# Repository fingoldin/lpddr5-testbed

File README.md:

# LPDDR5 testbed for the ZCU104

A single-channel LPDDR5X module (currently targeting SK hynix H58G56BK7BX068N or Samsung K3KL8L80CM-MGCT, both 2 x 16 Gb
with one rank) on a card that plugs into the ZCU104's DDR4
SO-DIMM socket and is driven by the FPGA through a dedicated pin map. It is a custom LPDDR5 card, not a DDR4 memory
module.

### Goals

Implement custon PHY and controller on ZCU104 FPGA, communicate with one rank on one channel of the LPDDR5 package at
the highest command rate possible (up to 800 MHz, DDR). Reads and writes can be slow, but must be at least 20 Mb/s 
(WCK = 10 MHz). 

### High-level signal routing

FPGA <-> LPDDR5 routes, for one channel and one rank with no DM wires:
- Bank 64 on FPGA: command bus and write data -- CK, CA0-6, CS0, RESET_n, WCK0/1, DQ0-15, plus PWR_EN and PGOOD
  (33 of 37 pins, socket fingers 108-162). LPDDR5 balls are connected via a resistive divider to level-shift the FPGA
  signals down to ~0.5 V from 1.2 V.
- Bank 66 on FPGA: read data and strobes -- 16 DQ with RDQS0/1 as true pairs (18 of 20 pairs, socket fingers 169-250).
  LPDDR5 balls are connected directly to FPGA P pins, while the corresponding N pins carry VREF_RD from a static DAC
  defining the read reference value around 170 mV.
- Bank 65 on FPGA: spare (0 of 44 pins, socket fingers 3-84), free to take DMI or a second channel later.

### Board components

Resistive dividers for 

### Operating notes

LPDDR5 allows CK down to 5 MHz (tCK max 200 ns), but the data rate is tied to CK (4x or 8x), so reads and writes run in
their own frequency set point: CK 25 MHz for 100 Mb/s reads, 80 MHz for 320 Mb/s writes. 800 MHz CK is for
command-only traffic.

### File layout

| Folder | Contents |
|---|---|
| `references/` | data sheets, user guides, the JEDEC text, models and vendor PCB guidelines used for the design (`references/README.md`) |

Derived from the Antmicro LPDDR5 testbed.

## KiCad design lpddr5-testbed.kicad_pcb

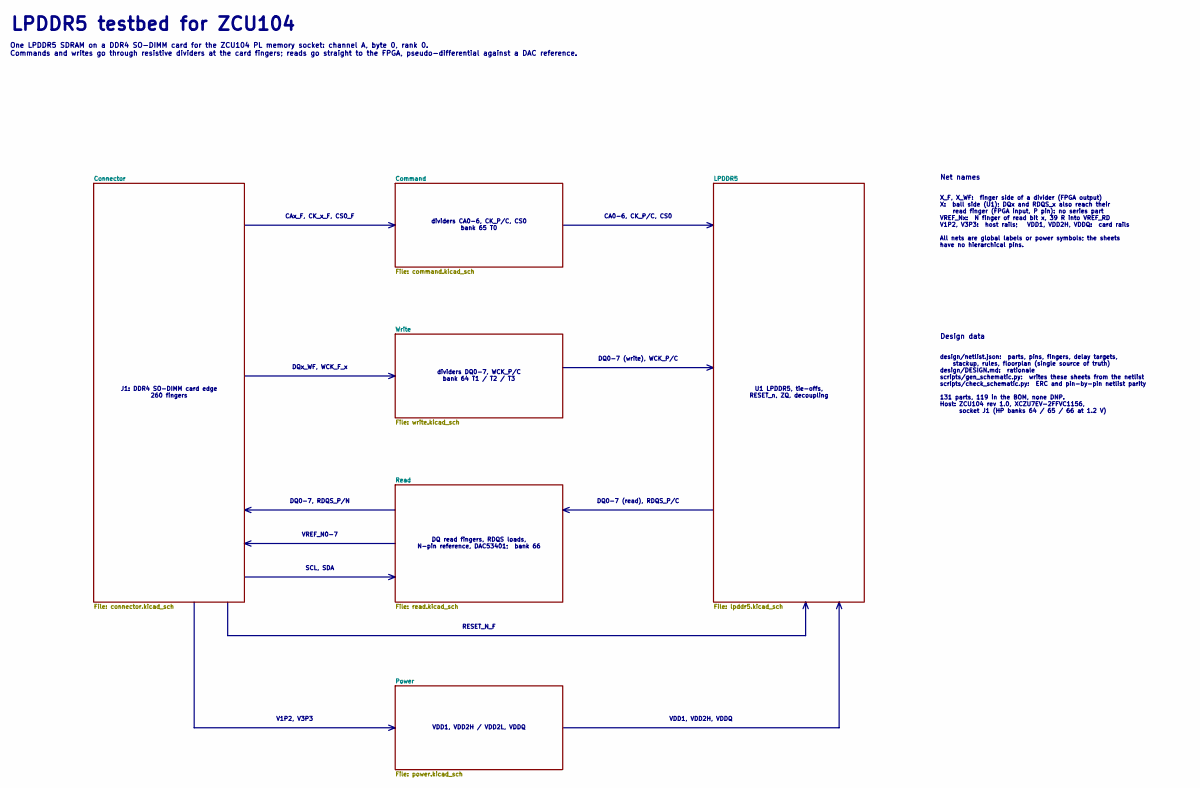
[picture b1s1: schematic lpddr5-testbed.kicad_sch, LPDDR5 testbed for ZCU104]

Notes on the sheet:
Net names
DQ0-7 (write), WCK_P/C
X_F, X_WF: finger side of a divider (FPGA output) X: ball side (U1); DQx and RDQS_x also reach their read finger (FPGA input, P pin): no series part VREF_Nx: N finger of read bit x, 39 R into VREF_RD V1P2, V3P3: host rails; VDD1, VDD2H, VDDQ: card rails All nets are global labels or power symbols; 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
DQ read fingers, RDQS loads, N-pin reference, DAC53401; bank 66
DQ0-7 (read), RDQS_P/C
CA0-6, CK_P/C, CS0
LPDDR5 testbed for ZCU104
CAx_F, CK_x_F, CS0_F
RESET_N_F
DQ0-7, RDQS_P/N
J1: DDR4 SO-DIMM card edge 260 fingers
V1P2, V3P3
VDD1, VDD2H / VDD2L, VDDQ
VREF_N0-7
Design data
SCL, SDA
design/netlist.json: parts, pins, fingers, delay targets, stackup, rules, floorplan (single source of truth) design/DESIGN.md: rationale scripts/gen_schematic.py: writes these sheets from the netlist scripts/check_schematic.py: ERC and pin-by-pin netlist parity 131 parts, 119 in the BOM, none DNP. 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
DQx_WF, WCK_F_x
dividers CA0-6, CK_P/C, CS0 bank 65 T0
dividers DQ0-7, WCK_P/C bank 64 T1 / T2 / T3
U1 LPDDR5, tie-offs, RESET_n, ZQ, decoupling
One LPDDR5 SDRAM on a DDR4 SO-DIMM card for the ZCU104 PL memory socket: channel A, byte 0, rank 0. Commands and writes go through resistive dividers at the card fingers; reads go straight to the FPGA, pseudo-differential against a DAC reference.
VDD1, VDD2H, VDDQ

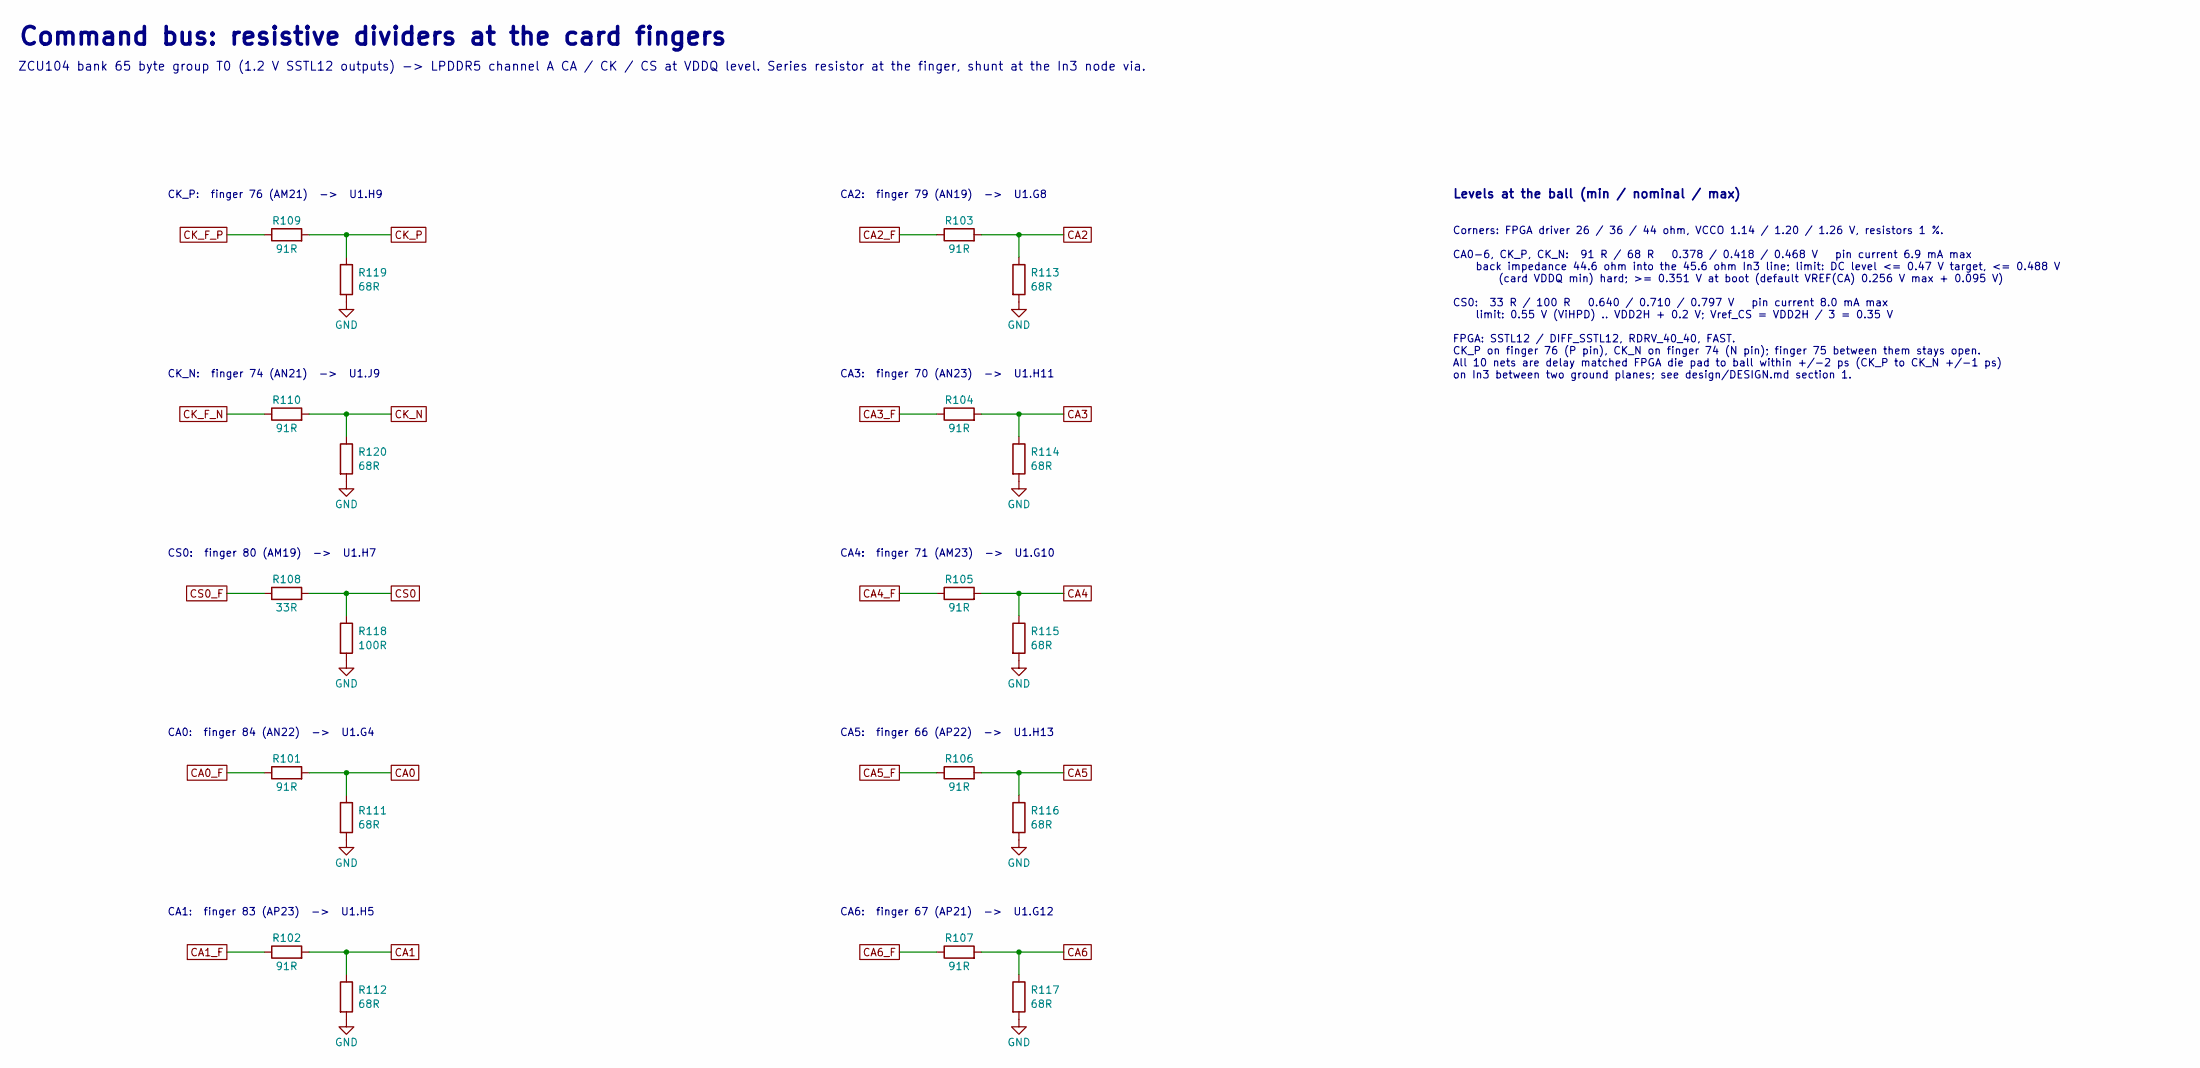
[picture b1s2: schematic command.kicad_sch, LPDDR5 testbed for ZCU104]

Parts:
R101, R102, R103, R104, R105, R106, R107, R109, R110: 91R; R_0201_0603Metric; MPN RC0201FR-0791RL
R108: 33R; R_0201_0603Metric; MPN RC0201FR-0733RL
R111, R112, R113, R114, R115, R116, R117, R119, R120: 68R; R_0201_0603Metric; MPN RC0201FR-0768RL
R118: 100R; R_0201_0603Metric; MPN RC0201FR-07100RL

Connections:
CA0: R101.2, R111.1; also elsewhere on the board
CA0_F: R101.1; also elsewhere on the board
CA1: R102.2, R112.1; also elsewhere on the board
CA1_F: R102.1; also elsewhere on the board
CA2: R103.2, R113.1; also elsewhere on the board
CA2_F: R103.1; also elsewhere on the board
CA3: R104.2, R114.1; also elsewhere on the board
CA3_F: R104.1; also elsewhere on the board
CA4: R105.2, R115.1; also elsewhere on the board
CA4_F: R105.1; also elsewhere on the board
CA5: R106.2, R116.1; also elsewhere on the board
CA5_F: R106.1; also elsewhere on the board
CA6: R107.2, R117.1; also elsewhere on the board
CA6_F: R107.1; also elsewhere on the board
CK_F_N: R110.1; also elsewhere on the board
CK_F_P: R109.1; also elsewhere on the board
CK_N: R110.2, R120.1; also elsewhere on the board
CK_P: R109.2, R119.1; also elsewhere on the board
CS0: R108.2, R118.1; also elsewhere on the board
CS0_F: R108.1; also elsewhere on the board
GND: R111.2, R112.2, R113.2, R114.2, R115.2, R116.2, R117.2, R118.2, R119.2, R120.2; also elsewhere on the board

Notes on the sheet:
CS0: finger 80 (AM19) -> U1.H7
CA0: finger 84 (AN22) -> U1.G4
Corners: FPGA driver 26 / 36 / 44 ohm, VCCO 1.14 / 1.20 / 1.26 V, resistors 1 %. CA0-6, CK_P, CK_N: 91 R / 68 R 0.378 / 0.418 / 0.468 V pin current 6.9 mA max back impedance 44.6 ohm into the 45.6 ohm In3 line; limit: DC level <= 0.47 V target, <= 0.488 V (card VDDQ min) hard; >= 0.351 V at boot (d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
CA6: finger 67 (AP21) -> U1.G12
Command bus: resistive dividers at the card fingers
CA4: finger 71 (AM23) -> U1.G10
CK_N: finger 74 (AN21) -> U1.J9
ZCU104 bank 65 byte group T0 (1.2 V SSTL12 outputs) -> LPDDR5 channel A CA / CK / CS at VDDQ level. Series resistor at the finger, shunt at the In3 node via.
CA1: finger 83 (AP23) -> U1.H5
Levels at the ball (min / nominal / max)
CK_P: finger 76 (AM21) -> U1.H9
CA2: finger 79 (AN19) -> U1.G8
CA5: finger 66 (AP22) -> U1.H13
CA3: finger 70 (AN23) -> U1.H11

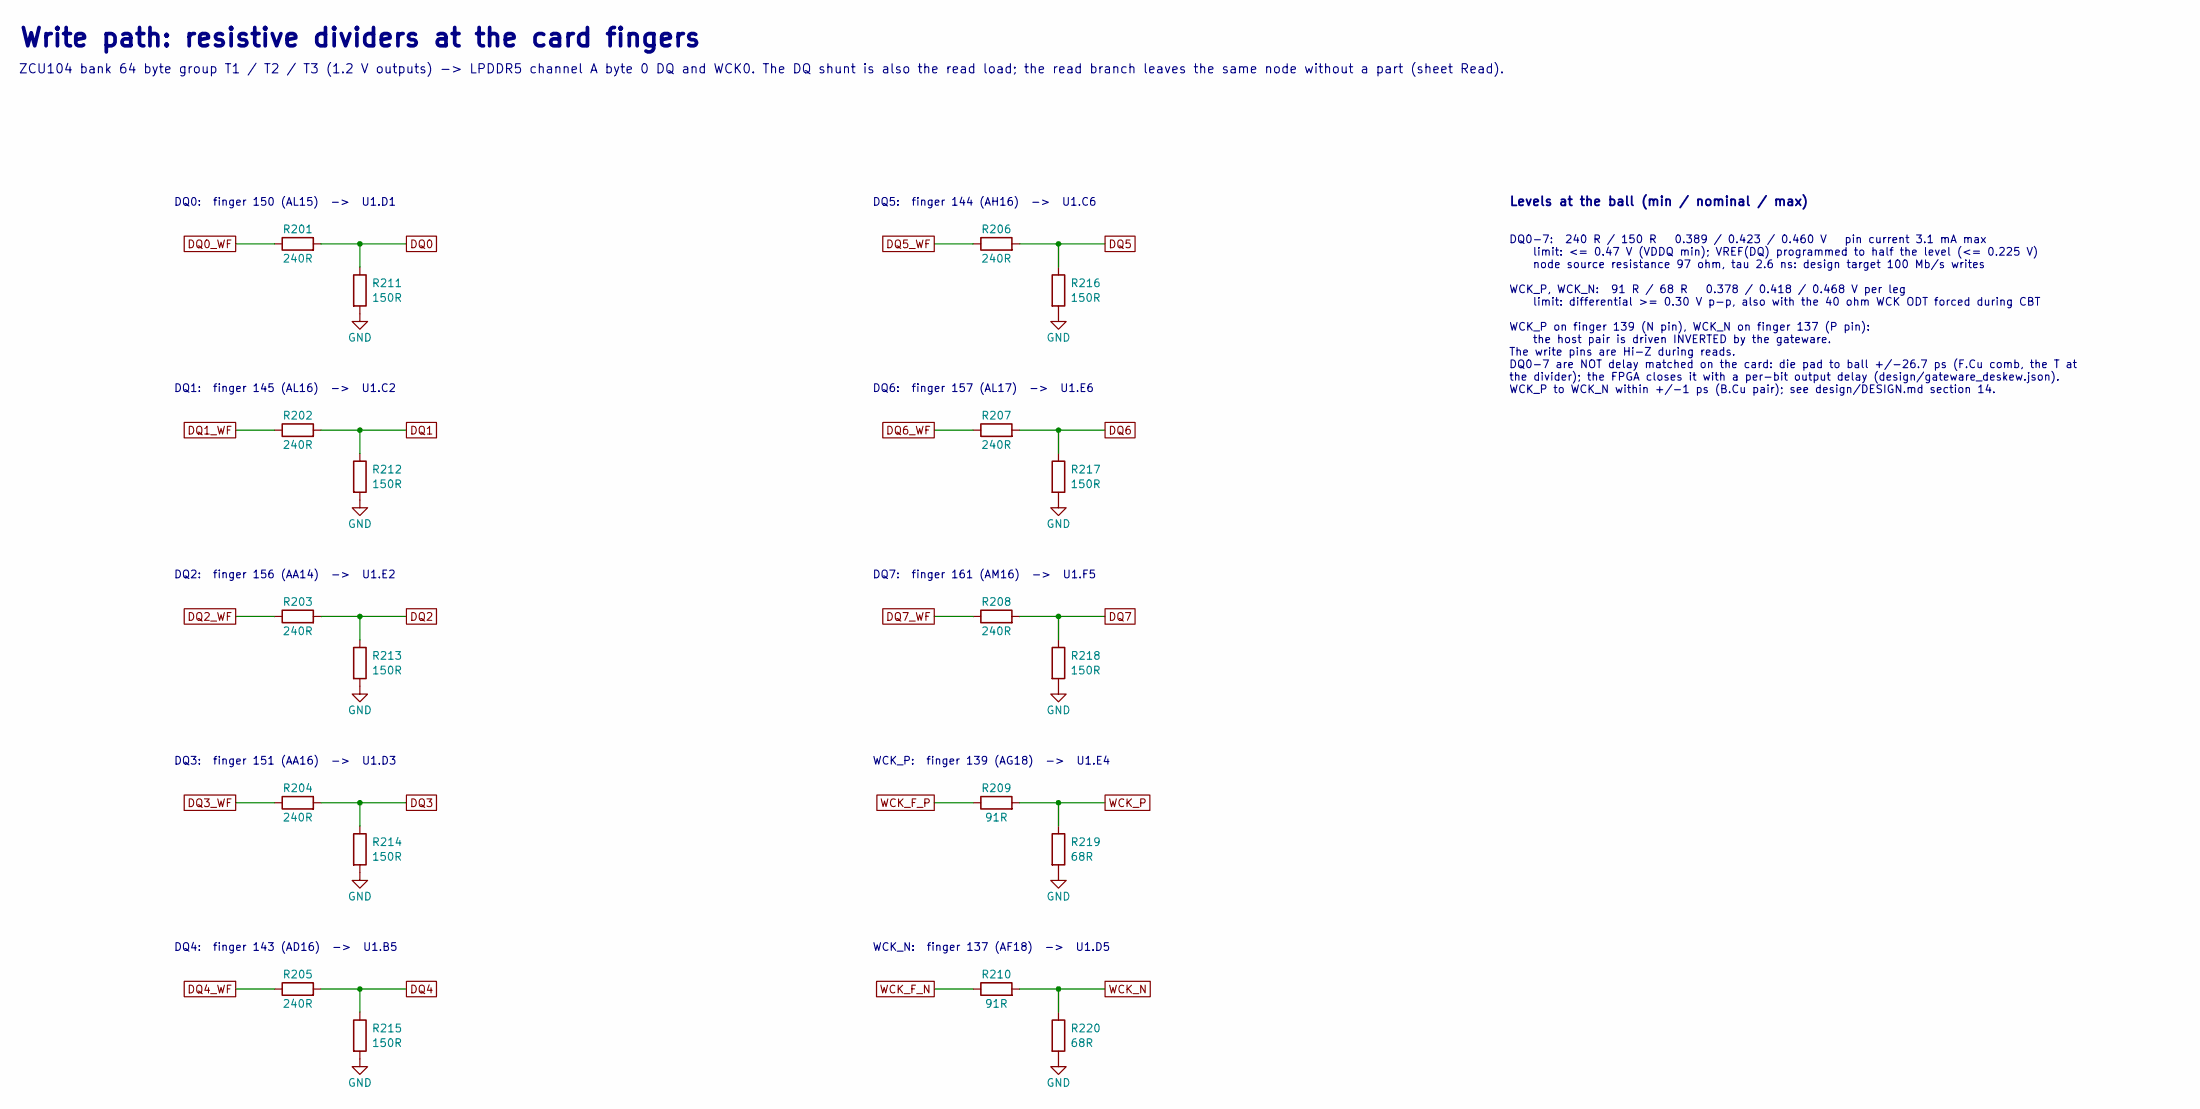
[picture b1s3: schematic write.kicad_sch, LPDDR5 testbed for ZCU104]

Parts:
R201, R202, R203, R204, R205, R206, R207, R208: 240R; R_0201_0603Metric; MPN RC0201FR-07240RL
R209, R210: 91R; R_0201_0603Metric; MPN RC0201FR-0791RL
R211, R212, R213, R214, R215, R216, R217, R218: 150R; R_0201_0603Metric; MPN RC0201FR-07150RL
R219, R220: 68R; R_0201_0603Metric; MPN RC0201FR-0768RL

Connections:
DQ0: R201.2, R211.1; also elsewhere on the board
DQ0_WF: R201.1; also elsewhere on the board
DQ1: R202.2, R212.1; also elsewhere on the board
DQ1_WF: R202.1; also elsewhere on the board
DQ2: R203.2, R213.1; also elsewhere on the board
DQ2_WF: R203.1; also elsewhere on the board
DQ3: R204.2, R214.1; also elsewhere on the board
DQ3_WF: R204.1; also elsewhere on the board
DQ4: R205.2, R215.1; also elsewhere on the board
DQ4_WF: R205.1; also elsewhere on the board
DQ5: R206.2, R216.1; also elsewhere on the board
DQ5_WF: R206.1; also elsewhere on the board
DQ6: R207.2, R217.1; also elsewhere on the board
DQ6_WF: R207.1; also elsewhere on the board
DQ7: R208.2, R218.1; also elsewhere on the board
DQ7_WF: R208.1; also elsewhere on the board
GND: R211.2, R212.2, R213.2, R214.2, R215.2, R216.2, R217.2, R218.2, R219.2, R220.2; also elsewhere on the board
WCK_F_N: R210.1; also elsewhere on the board
WCK_F_P: R209.1; also elsewhere on the board
WCK_N: R210.2, R220.1; also elsewhere on the board
WCK_P: R209.2, R219.1; also elsewhere on the board

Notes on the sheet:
DQ4: finger 143 (AD16) -> U1.B5
ZCU104 bank 64 byte group T1 / T2 / T3 (1.2 V outputs) -> LPDDR5 channel A byte 0 DQ and WCK0. The DQ shunt is also the read load; the read branch leaves the same node without a part (sheet Read).
DQ5: finger 144 (AH16) -> U1.C6
Write path: resistive dividers at the card fingers
DQ6: finger 157 (AL17) -> U1.E6
DQ0: finger 150 (AL15) -> U1.D1
WCK_N: finger 137 (AF18) -> U1.D5
DQ7: finger 161 (AM16) -> U1.F5
DQ1: finger 145 (AL16) -> U1.C2
DQ2: finger 156 (AA14) -> U1.E2
Levels at the ball (min / nominal / max)
DQ3: finger 151 (AA16) -> U1.D3
DQ0-7: 240 R / 150 R 0.389 / 0.423 / 0.460 V pin current 3.1 mA max limit: <= 0.47 V (VDDQ min); VREF(DQ) programmed to half the level (<= 0.225 V) node source resistance 97 ohm, tau 2.6 ns: design target 100 Mb/s writes WCK_P, WCK_N: 91 R / 68 R 0.378 / 0.418 / 0.468 V per leg limit: differential 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
WCK_P: finger 139 (AG18) -> U1.E4

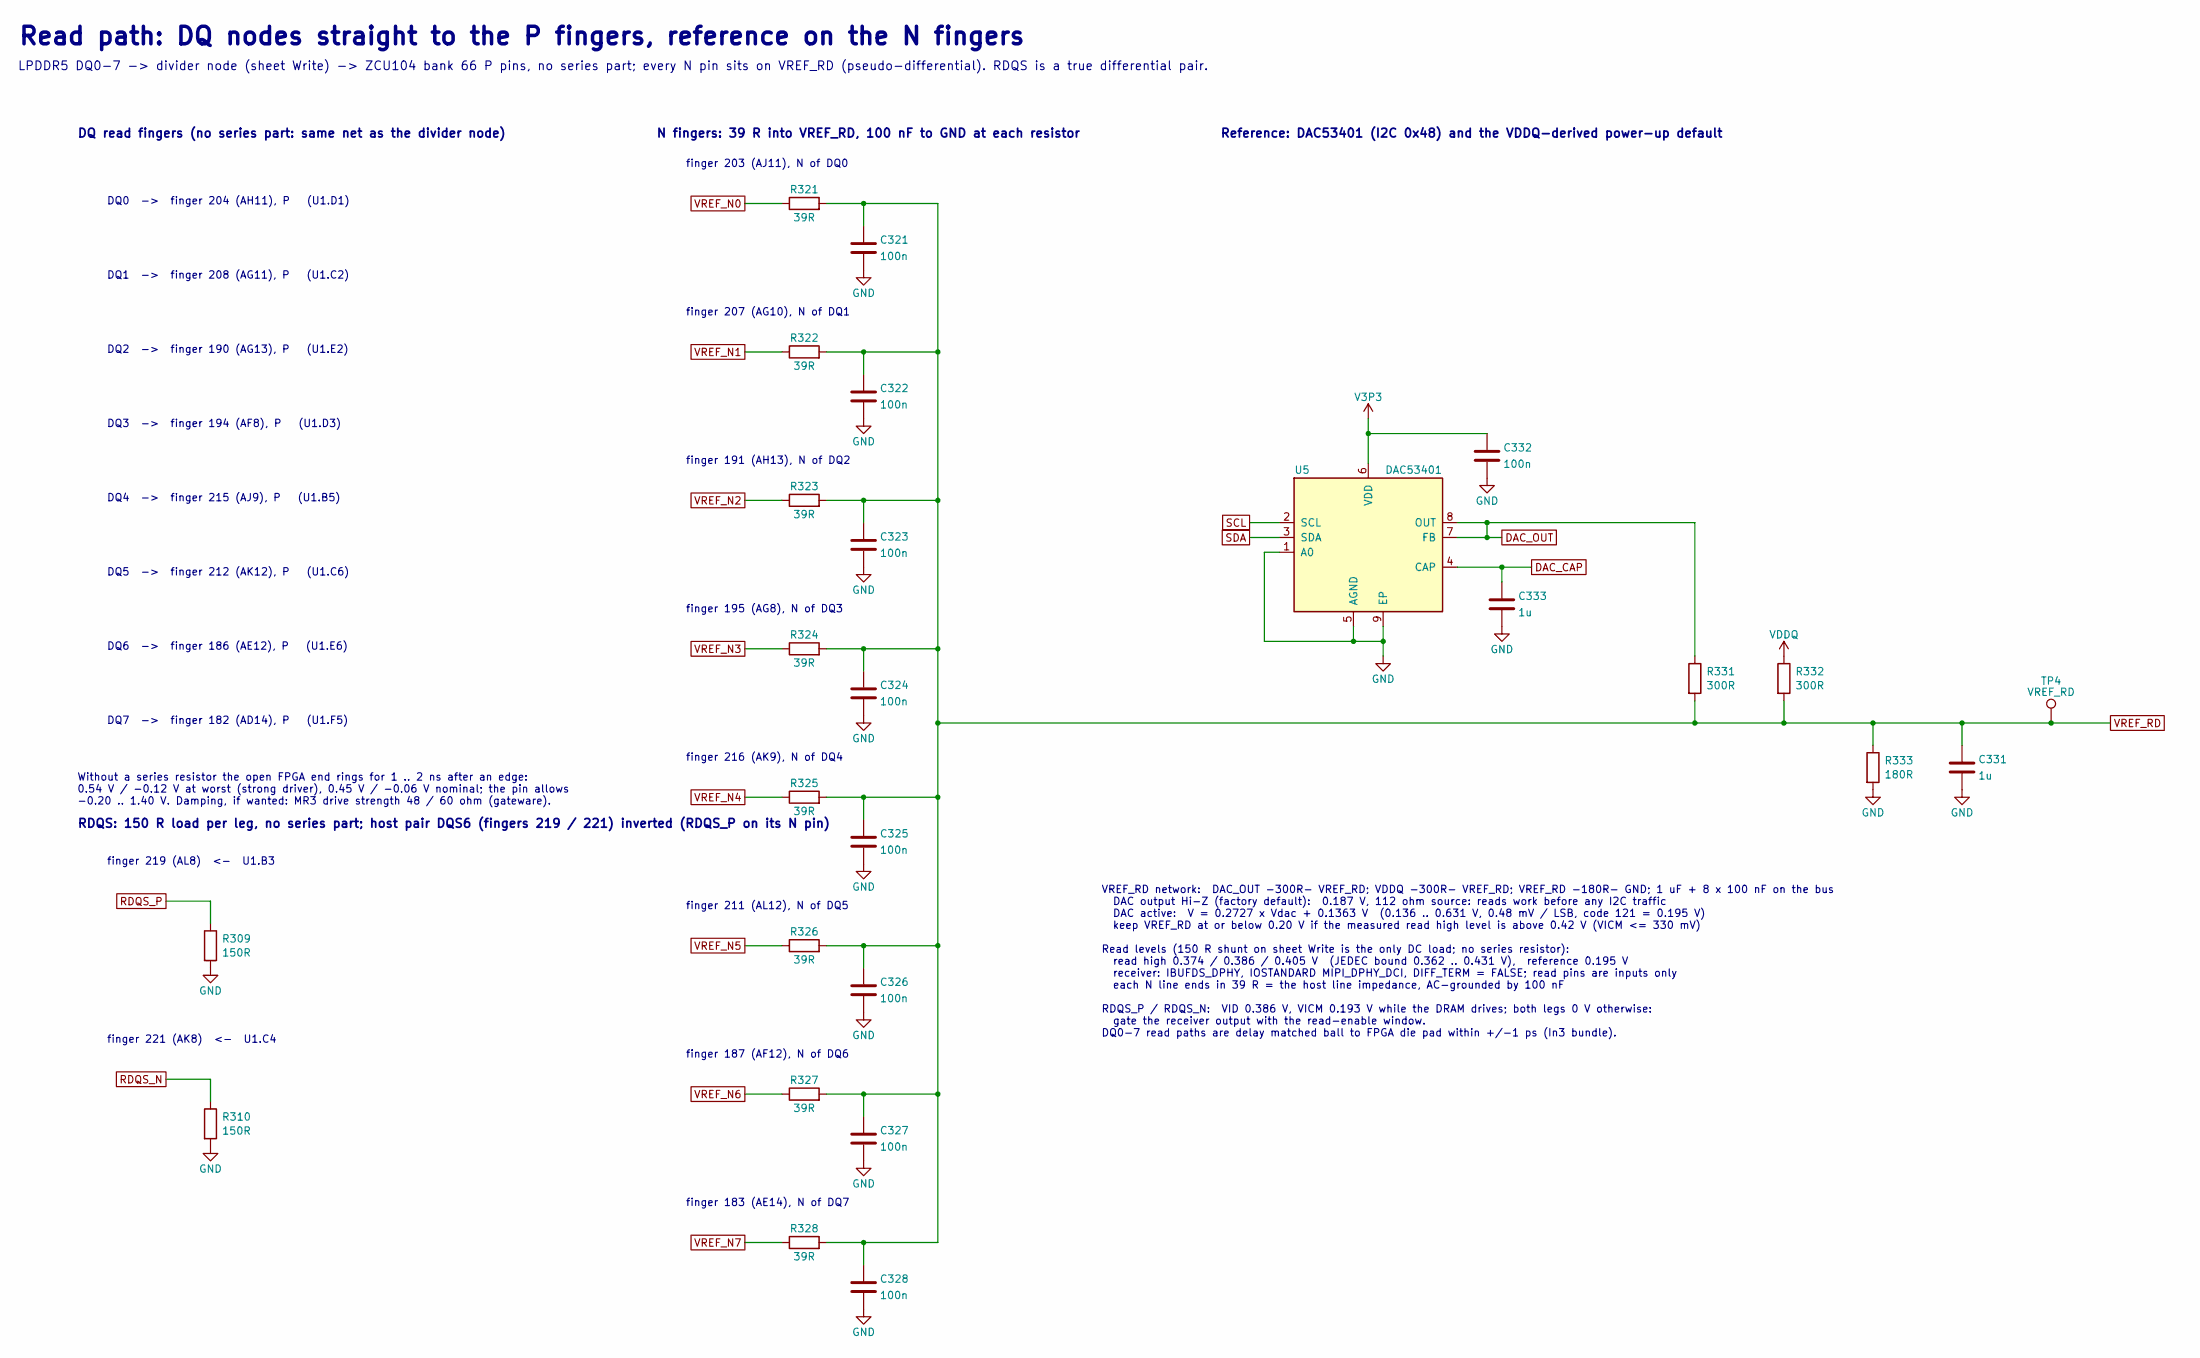
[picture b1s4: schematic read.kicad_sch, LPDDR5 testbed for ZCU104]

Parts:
C321, C322, C323, C324, C325, C326, C327, C328: 100n; C_0201_0603Metric; MPN CL03A104KQ3NNNC
C331, C333: 1u; C_0402_1005Metric; MPN CL05A105KP5NNNC
C332: 100n; C_0402_1005Metric; MPN CL05B104KO5NNNC
R309, R310: 150R; R_0201_0603Metric; MPN RC0201FR-07150RL
R321, R322, R323, R324, R325, R326, R327, R328: 39R; R_0201_0603Metric; MPN RC0201FR-0739RL
R331, R332: 300R; R_0402_1005Metric; MPN RC0402FR-07300RL
R333: 180R; R_0402_1005Metric; MPN RC0402FR-07180RL
TP4: VREF_RD; TestPoint_Pad_D1.0mm; MPN N/A (PCB pad)
U5: DAC53401; WSON-8-1EP_2x2mm_P0.5mm_EP0.9x1.6mm; MPN DAC53401DSGR

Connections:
DAC_CAP: C333.1, U5.4 (CAP)
DAC_OUT: R331.1, U5.7 (FB), U5.8 (OUT)
GND: C321.2, C322.2, C323.2, C324.2, C325.2, C326.2, C327.2, C328.2, C331.2, C332.2, C333.2, R309.2, R310.2, R333.2, U5.1 (A0), U5.5 (AGND), U5.9 (EP); also elsewhere on the board
RDQS_N: R310.1; also elsewhere on the board
RDQS_P: R309.1; also elsewhere on the board
SCL: U5.2 (SCL); also elsewhere on the board
SDA: U5.3 (SDA); also elsewhere on the board
V3P3: C332.1, U5.6 (VDD); also elsewhere on the board
VDDQ: R332.1; also elsewhere on the board
VREF_N0: R321.1; also elsewhere on the board
VREF_N1: R322.1; also elsewhere on the board
VREF_N2: R323.1; also elsewhere on the board
VREF_N3: R324.1; also elsewhere on the board
VREF_N4: R325.1; also elsewhere on the board
VREF_N5: R326.1; also elsewhere on the board
VREF_N6: R327.1; also elsewhere on the board
VREF_N7: R328.1; also elsewhere on the board
VREF_RD: C321.1, C322.1, C323.1, C324.1, C325.1, C326.1, C327.1, C328.1, C331.1, R321.2, R322.2, R323.2, R324.2, R325.2, R326.2, R327.2, R328.2, R331.2, R332.2, R333.1, TP4.1

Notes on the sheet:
DQ7 -> finger 182 (AD14), P (U1.F5)
DQ1 -> finger 208 (AG11), P (U1.C2)
Reference: DAC53401 (I2C 0x48) and the VDDQ-derived power-up default
RDQS: 150 R load per leg, no series part; host pair DQS6 (fingers 219 / 221) inverted (RDQS_P on its N pin)
Without a series resistor the open FPGA end rings for 1 .. 2 ns after an edge: 0.54 V / -0.12 V at worst (strong driver), 0.45 V / -0.06 V nominal; the pin allows -0.20 .. 1.40 V. Damping, if wanted: MR3 drive strength 48 / 60 ohm (gateware).
N fingers: 39 R into VREF_RD, 100 nF to GND at each resistor
LPDDR5 DQ0-7 -> divider node (sheet Write) -> ZCU104 bank 66 P pins, no series part; every N pin sits on VREF_RD (pseudo-differential). RDQS is a true differential pair.
VREF_RD network: DAC_OUT -300R- VREF_RD; VDDQ -300R- VREF_RD; VREF_RD -180R- GND; 1 uF + 8 x 100 nF on the bus DAC output Hi-Z (factory default): 0.187 V, 112 ohm source: reads work before any I2C traffic DAC active: V = 0.2727 x Vdac + 0.1363 V (0.136 .. 0.631 V, 0.48 mV / LSB, code 121 = 0.195 V)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
finger 195 (AG8), N of DQ3
DQ2 -> finger 190 (AG13), P (U1.E2)
finger 211 (AL12), N of DQ5
finger 203 (AJ11), N of DQ0
finger 191 (AH13), N of DQ2
finger 221 (AK8) <- U1.C4
DQ0 -> finger 204 (AH11), P (U1.D1)
DQ5 -> finger 212 (AK12), P (U1.C6)
DQ6 -> finger 186 (AE12), P (U1.E6)
DQ4 -> finger 215 (AJ9), P (U1.B5)
finger 183 (AE14), N of DQ7
DQ read fingers (no series part: same net as the divider node)
finger 207 (AG10), N of DQ1
Read path: DQ nodes straight to the P fingers, reference on the N fingers
finger 216 (AK9), N of DQ4
finger 219 (AL8) <- U1.B3
DQ3 -> finger 194 (AF8), P (U1.D3)
finger 187 (AF12), N of DQ6

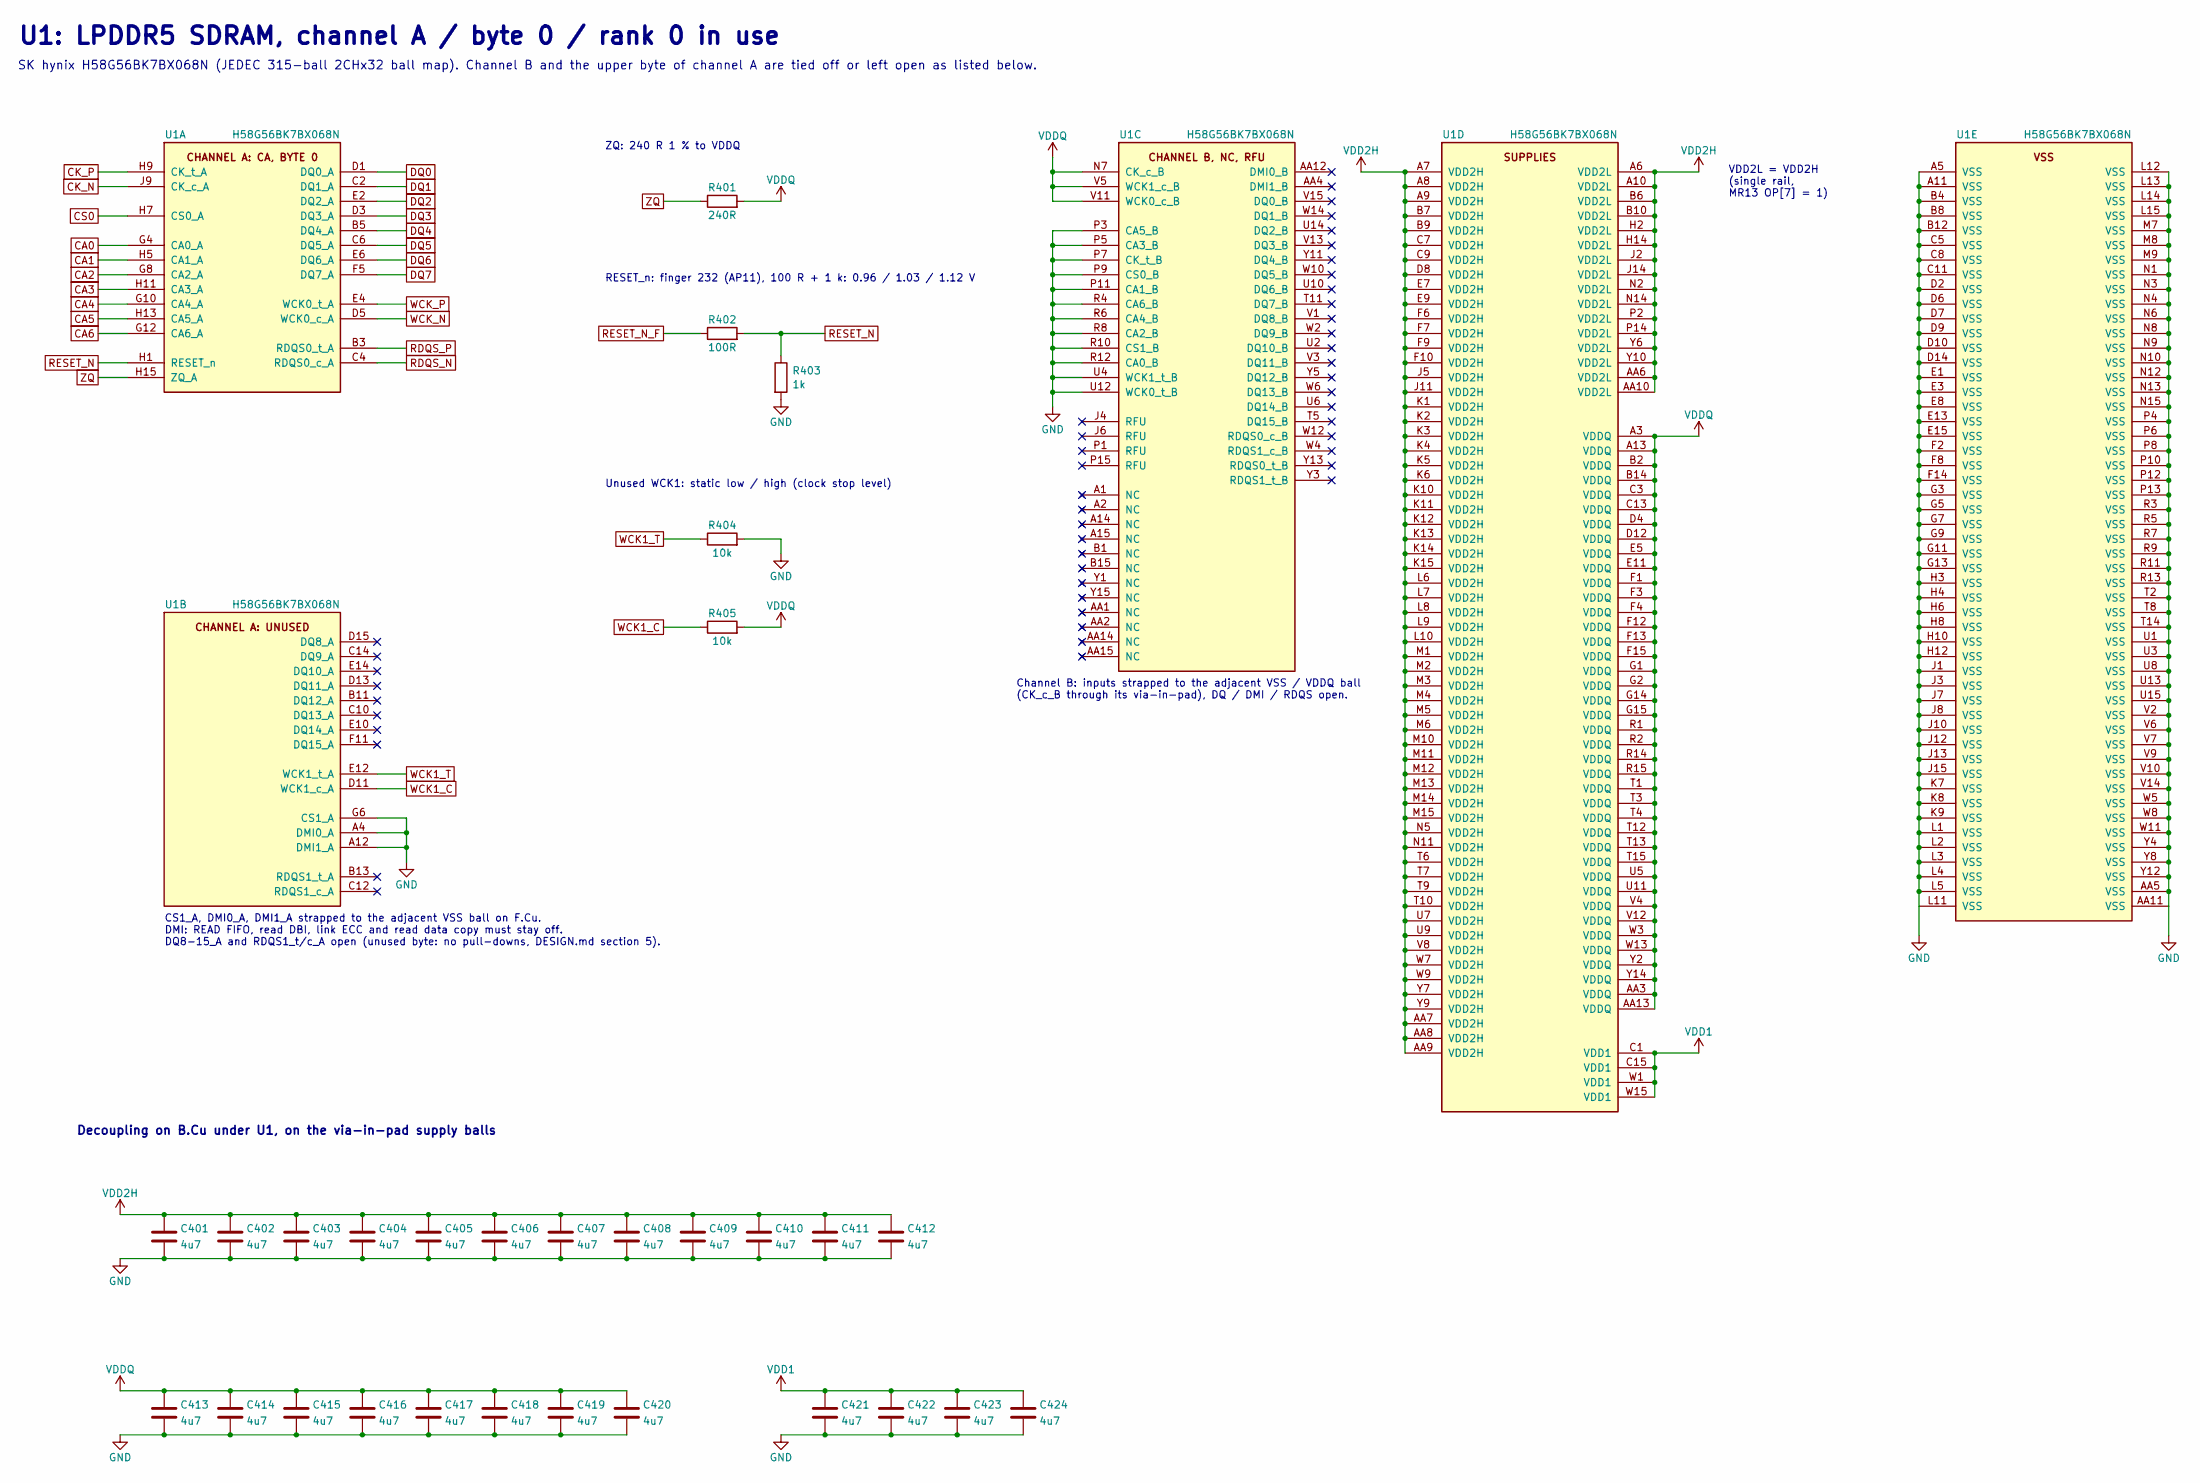
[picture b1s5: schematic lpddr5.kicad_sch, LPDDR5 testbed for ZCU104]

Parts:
C401, C402, C403, C404, C405, C406, C407, C408, C409, C410, C411, C412, C413, C414, C415, C416, C417, C418, C419, C420, C421, C422, C423, C424: 4u7; C_0402_1005Metric; MPN CL05A475MP5NRNC
R401: 240R; R_0201_0603Metric; MPN RC0201FR-07240RL
R402: 100R; R_0201_0603Metric; MPN RC0201FR-07100RL
R403: 1k; R_0402_1005Metric; MPN RC0402FR-071KL
R404, R405: 10k; R_0402_1005Metric; MPN RC0402FR-0710KL
U1: H58G56BK7BX068N; BGA-315_12.4x15mm_P0.8x0.7mm; MPN H58G56BK7BX068N

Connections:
CA0: U1.G4 (CA0_A); also elsewhere on the board
CA1: U1.H5 (CA1_A); also elsewhere on the board
CA2: U1.G8 (CA2_A); also elsewhere on the board
CA3: U1.H11 (CA3_A); also elsewhere on the board
CA4: U1.G10 (CA4_A); also elsewhere on the board
CA5: U1.H13 (CA5_A); also elsewhere on the board
CA6: U1.G12 (CA6_A); also elsewhere on the board
CK_N: U1.J9 (CK_c_A); also elsewhere on the board
CK_P: U1.H9 (CK_t_A); also elsewhere on the board
CS0: U1.H7 (CS0_A); also elsewhere on the board
DQ0: U1.D1 (DQ0_A); also elsewhere on the board
DQ1: U1.C2 (DQ1_A); also elsewhere on the board
DQ2: U1.E2 (DQ2_A); also elsewhere on the board
DQ3: U1.D3 (DQ3_A); also elsewhere on the board
DQ4: U1.B5 (DQ4_A); also elsewhere on the board
DQ5: U1.C6 (DQ5_A); also elsewhere on the board
DQ6: U1.E6 (DQ6_A); also elsewhere on the board
DQ7: U1.F5 (DQ7_A); also elsewhere on the board
GND: C401.2, C402.2, C403.2, C404.2, C405.2, C406.2, C407.2, C408.2, C409.2, C410.2, C411.2, C412.2, C413.2, C414.2, C415.2, C416.2, C417.2, C418.2, C419.2, C420.2, C421.2, C422.2, C423.2, C424.2, R403.2, R404.2, U1.A4 (DMI0_A), U1.A5 (VSS), U1.A11 (VSS), U1.A12 (DMI1_A), U1.AA5 (VSS), U1.AA11 (VSS), U1.B4 (VSS), U1.B8 (VSS), U1.B12 (VSS), U1.C5 (VSS), U1.C8 (VSS), U1.C11 (VSS), U1.D2 (VSS), U1.D6 (VSS), U1.D7 (VSS), U1.D9 (VSS), U1.D10 (VSS), U1.D14 (VSS), U1.E1 (VSS), U1.E3 (VSS), U1.E8 (VSS), U1.E13 (VSS), U1.E15 (VSS), U1.F2 (VSS), U1.F8 (VSS), U1.F14 (VSS), U1.G3 (VSS), U1.G5 (VSS), U1.G6 (CS1_A), U1.G7 (VSS), U1.G9 (VSS), U1.G11 (VSS), U1.G13 (VSS), U1.H3 (VSS), U1.H4 (VSS), U1.H6 (VSS), U1.H8 (VSS), U1.H10 (VSS), U1.H12 (VSS), U1.J1 (VSS), U1.J3 (VSS), U1.J7 (VSS), U1.J8 (VSS), U1.J10 (VSS), U1.J12 (VSS), U1.J13 (VSS), U1.J15 (VSS), U1.K7 (VSS), U1.K8 (VSS), U1.K9 (VSS), U1.L1 (VSS), U1.L2 (VSS), U1.L3 (VSS), U1.L4 (VSS), U1.L5 (VSS), U1.L11 (VSS), U1.L12 (VSS), U1.L13 (VSS), U1.L14 (VSS), U1.L15 (VSS), U1.M7 (VSS), U1.M8 (VSS), U1.M9 (VSS), U1.N1 (VSS), U1.N3 (VSS), U1.N4 (VSS), U1.N6 (VSS), U1.N8 (VSS), U1.N9 (VSS), U1.N10 (VSS), U1.N12 (VSS), U1.N13 (VSS), U1.N15 (VSS), U1.P3 (CA5_B), U1.P4 (VSS), U1.P5 (CA3_B), U1.P6 (VSS), U1.P7 (CK_t_B), U1.P8 (VSS), U1.P9 (CS0_B), U1.P10 (VSS), U1.P11 (CA1_B), U1.P12 (VSS), U1.P13 (VSS), U1.R3 (VSS), U1.R4 (CA6_B), U1.R5 (VSS), U1.R6 (CA4_B), U1.R7 (VSS), U1.R8 (CA2_B), U1.R9 (VSS), U1.R10 (CS1_B), U1.R11 (VSS), U1.R12 (CA0_B), U1.R13 (VSS), U1.T2 (VSS), U1.T8 (VSS), U1.T14 (VSS), U1.U1 (VSS), U1.U3 (VSS), U1.U4 (WCK1_t_B), U1.U8 (VSS), U1.U12 (WCK0_t_B), U1.U13 (VSS), U1.U15 (VSS), U1.V2 (VSS), U1.V6 (VSS), U1.V7 (VSS), U1.V9 (VSS), U1.V10 (VSS), U1.V14 (VSS), U1.W5 (VSS), U1.W8 (VSS), U1.W11 (VSS), U1.Y4 (VSS), U1.Y8 (VSS), U1.Y12 (VSS); also elsewhere on the board
RDQS_N: U1.C4 (RDQS0_c_A); also elsewhere on the board
RDQS_P: U1.B3 (RDQS0_t_A); also elsewhere on the board
RESET_N: R402.2, R403.1, U1.H1 (RESET_n)
RESET_N_F: R402.1; also elsewhere on the board
VDD1: C421.1, C422.1, C423.1, C424.1, U1.C1 (VDD1), U1.C15 (VDD1), U1.W1 (VDD1), U1.W15 (VDD1); also elsewhere on the board
VDD2H: C401.1, C402.1, C403.1, C404.1, C405.1, C406.1, C407.1, C408.1, C409.1, C410.1, C411.1, C412.1, U1.A6 (VDD2L), U1.A7 (VDD2H), U1.A8 (VDD2H), U1.A9 (VDD2H), U1.A10 (VDD2L), U1.AA6 (VDD2L), U1.AA7 (VDD2H), U1.AA8 (VDD2H), U1.AA9 (VDD2H), U1.AA10 (VDD2L), U1.B6 (VDD2L), U1.B7 (VDD2H), U1.B9 (VDD2H), U1.B10 (VDD2L), U1.C7 (VDD2H), U1.C9 (VDD2H), U1.D8 (VDD2H), U1.E7 (VDD2H), U1.E9 (VDD2H), U1.F6 (VDD2H), U1.F7 (VDD2H), U1.F9 (VDD2H), U1.F10 (VDD2H), U1.H2 (VDD2L), U1.H14 (VDD2L), U1.J2 (VDD2L), U1.J5 (VDD2H), U1.J11 (VDD2H), U1.J14 (VDD2L), U1.K1 (VDD2H), U1.K2 (VDD2H), U1.K3 (VDD2H), U1.K4 (VDD2H), U1.K5 (VDD2H), U1.K6 (VDD2H), U1.K10 (VDD2H), U1.K11 (VDD2H), U1.K12 (VDD2H), U1.K13 (VDD2H), U1.K14 (VDD2H), U1.K15 (VDD2H), U1.L6 (VDD2H), U1.L7 (VDD2H), U1.L8 (VDD2H), U1.L9 (VDD2H), U1.L10 (VDD2H), U1.M1 (VDD2H), U1.M2 (VDD2H), U1.M3 (VDD2H), U1.M4 (VDD2H), U1.M5 (VDD2H), U1.M6 (VDD2H), U1.M10 (VDD2H), U1.M11 (VDD2H), U1.M12 (VDD2H), U1.M13 (VDD2H), U1.M14 (VDD2H), U1.M15 (VDD2H), U1.N2 (VDD2L), U1.N5 (VDD2H), U1.N11 (VDD2H), U1.N14 (VDD2L), U1.P2 (VDD2L), U1.P14 (VDD2L), U1.T6 (VDD2H), U1.T7 (VDD2H), U1.T9 (VDD2H), U1.T10 (VDD2H), U1.U7 (VDD2H), U1.U9 (VDD2H), U1.V8 (VDD2H), U1.W7 (VDD2H), U1.W9 (VDD2H), U1.Y6 (VDD2L), U1.Y7 (VDD2H), U1.Y9 (VDD2H), U1.Y10 (VDD2L); also elsewhere on the board
VDDQ: C413.1, C414.1, C415.1, C416.1, C417.1, C418.1, C419.1, C420.1, R401.2, R405.2, U1.A3 (VDDQ), U1.A13 (VDDQ), U1.AA3 (VDDQ), U1.AA13 (VDDQ), U1.B2 (VDDQ), U1.B14 (VDDQ), U1.C3 (VDDQ), U1.C13 (VDDQ), U1.D4 (VDDQ), U1.D12 (VDDQ), U1.E5 (VDDQ), U1.E11 (VDDQ), U1.F1 (VDDQ), U1.F3 (VDDQ), U1.F4 (VDDQ), U1.F12 (VDDQ), U1.F13 (VDDQ), U1.F15 (VDDQ), U1.G1 (VDDQ), U1.G2 (VDDQ), U1.G14 (VDDQ), U1.G15 (VDDQ), U1.N7 (CK_c_B), U1.R1 (VDDQ), U1.R2 (VDDQ), U1.R14 (VDDQ), U1.R15 (VDDQ), U1.T1 (VDDQ), U1.T3 (VDDQ), U1.T4 (VDDQ), U1.T12 (VDDQ), U1.T13 (VDDQ), U1.T15 (VDDQ), U1.U5 (VDDQ), U1.U11 (VDDQ), U1.V4 (VDDQ), U1.V5 (WCK1_c_B), U1.V11 (WCK0_c_B), U1.V12 (VDDQ), U1.W3 (VDDQ), U1.W13 (VDDQ), U1.Y2 (VDDQ), U1.Y14 (VDDQ); also elsewhere on the board
WCK1_C: R405.1, U1.D11 (WCK1_c_A)
WCK1_T: R404.1, U1.E12 (WCK1_t_A)
WCK_N: U1.D5 (WCK0_c_A); also elsewhere on the board
WCK_P: U1.E4 (WCK0_t_A); also elsewhere on the board
ZQ: R401.1, U1.H15 (ZQ_A)

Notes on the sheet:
CS1_A, DMI0_A, DMI1_A strapped to the adjacent VSS ball on F.Cu. DMI: READ FIFO, read DBI, link ECC and read data copy must stay off. DQ8-15_A and RDQS1_t/c_A open (unused byte: no pull-downs, DESIGN.md section 5).
VDD2L = VDD2H (single rail, MR13 OP[7] = 1)
RESET_n: finger 232 (AP11), 100 R + 1 k: 0.96 / 1.03 / 1.12 V
SK hynix H58G56BK7BX068N (JEDEC 315-ball 2CHx32 ball map). Channel B and the upper byte of channel A are tied off or left open as listed below.
Unused WCK1: static low / high (clock stop level)
ZQ: 240 R 1 % to VDDQ
Decoupling on B.Cu under U1, on the via-in-pad supply balls
Channel B: inputs strapped to the adjacent VSS / VDDQ ball (CK_c_B through its via-in-pad), DQ / DMI / RDQS open.
U1: LPDDR5 SDRAM, channel A / byte 0 / rank 0 in use

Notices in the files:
parts and their libraries:
License: Apache-2.0
